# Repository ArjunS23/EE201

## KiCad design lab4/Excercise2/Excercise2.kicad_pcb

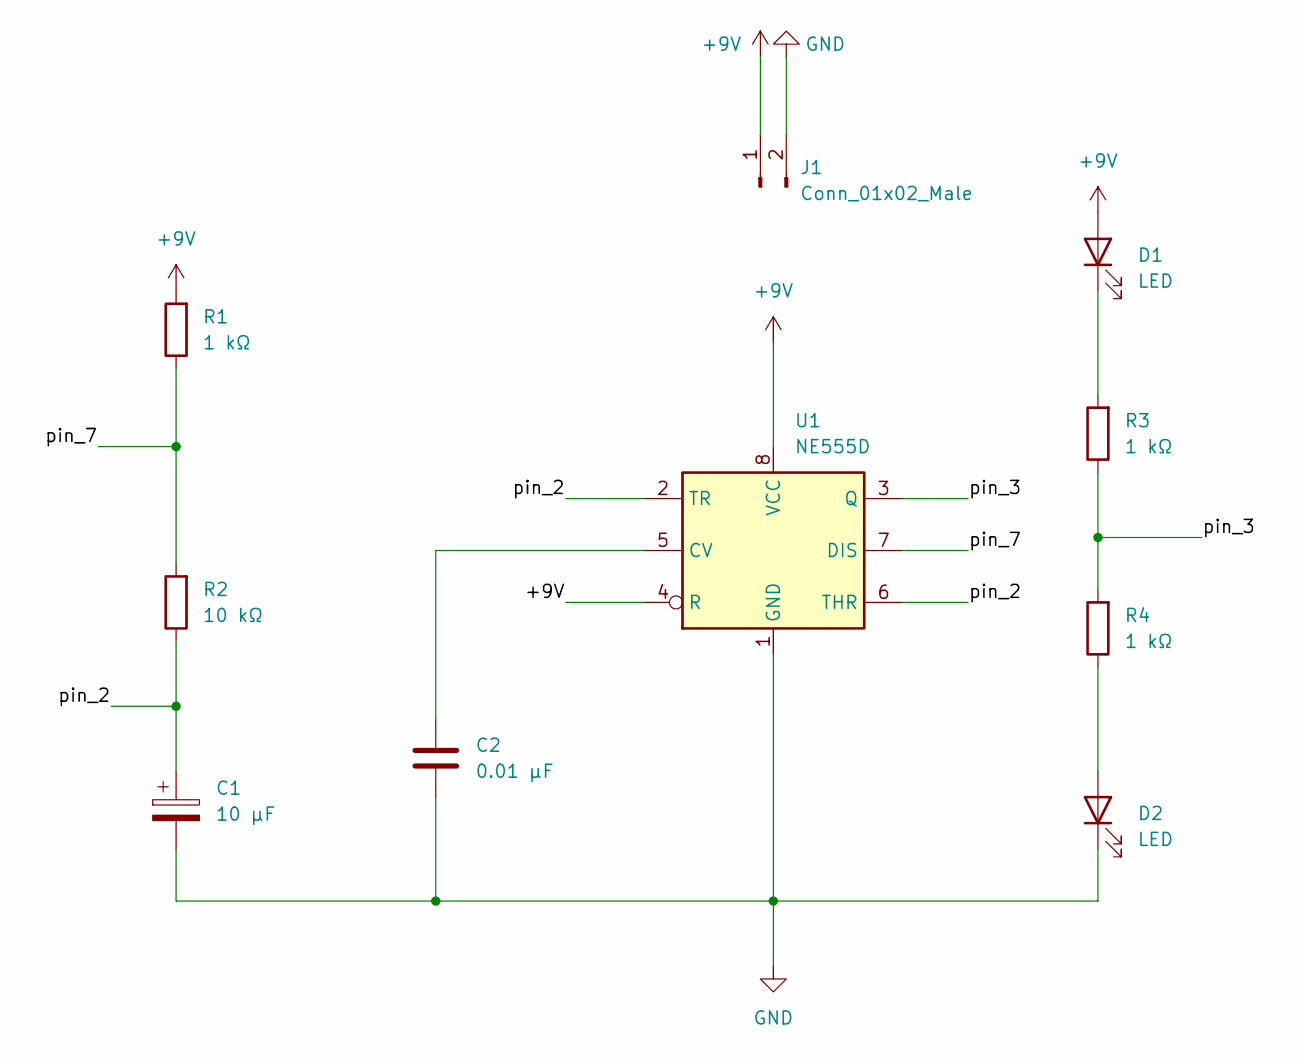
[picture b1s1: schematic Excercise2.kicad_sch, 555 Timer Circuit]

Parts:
C1: 10 μF; CP_EIA-3216-18_Kemet-A_Pad1.58x1.35mm_HandSolder
C2: 0.01 μF; C_0805_2012Metric_Pad1.18x1.45mm_HandSolder
D1, D2: LED; LED_1206_3216Metric_Pad1.42x1.75mm_HandSolder
J1: Conn_01x02_Male; TerminalBlock_bornier-2_P5.08mm
R1, R3, R4: 1 kΩ; R_0805_2012Metric_Pad1.20x1.40mm_HandSolder
R2: 10 kΩ; R_0805_2012Metric_Pad1.20x1.40mm_HandSolder
U1: NE555D; SOIC-8-1EP_3.9x4.9mm_P1.27mm_EP2.29x3mm

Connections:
+9V: D1.2 (A), J1.1, R1.2, U1.4 (R), U1.8 (VCC)
/pin_2: C1.1, R2.1, U1.2 (TR), U1.6 (THR)
/pin_3: R3.1, R4.2, U1.3 (Q)
/pin_7: R1.1, R2.2, U1.7 (DIS)
GND: C1.2, C2.2, D2.1 (K), J1.2, U1.1 (GND)
unnamed: C2.1, U1.5 (CV)
unnamed: D1.1 (K), R3.2
unnamed: D2.2 (A), R4.1

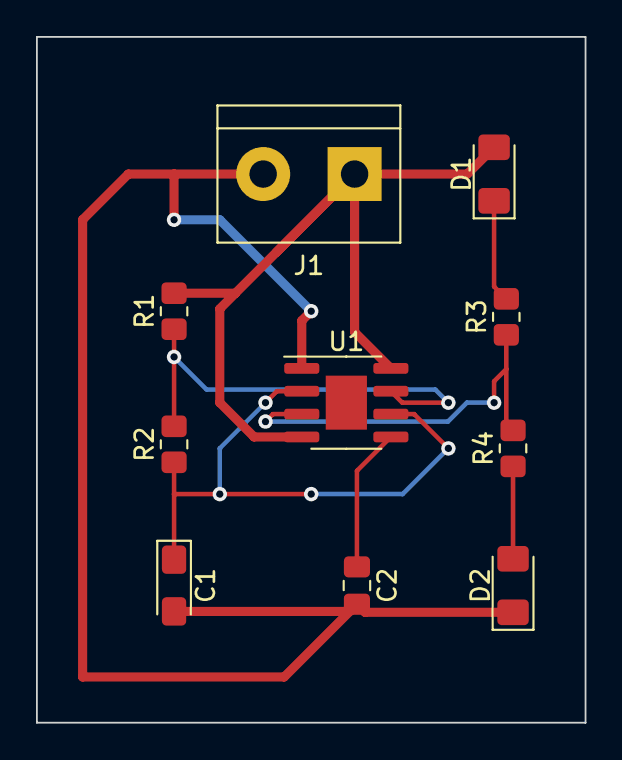
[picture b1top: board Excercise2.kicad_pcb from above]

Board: 2 copper layers, 30.5 x 38.1 mm, 10 parts (0 on the bottom side), 8 nets.

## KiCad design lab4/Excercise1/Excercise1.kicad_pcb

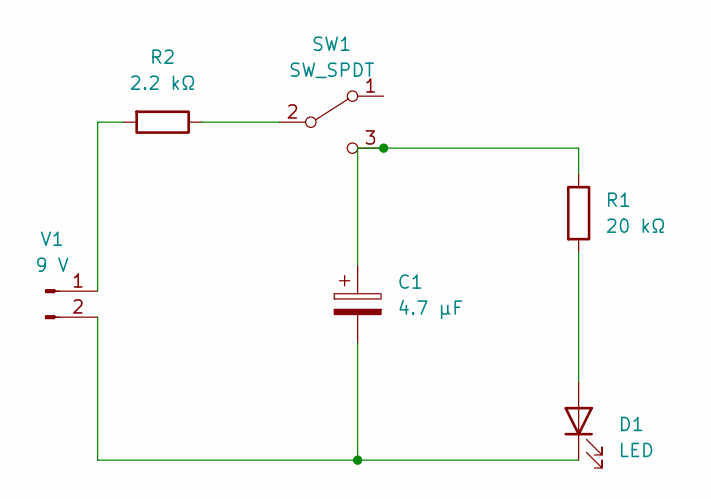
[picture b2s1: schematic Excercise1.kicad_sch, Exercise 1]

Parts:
C1: 4.7 μF; C_Radial_D5.0mm_H5.0mm_P2.00mm
D1: LED; LED_D5.0mm
R1: 20 kΩ; R_Axial_DIN0516_L15.5mm_D5.0mm_P20.32mm_Horizontal
R2: 2.2 kΩ; R_Axial_DIN0516_L15.5mm_D5.0mm_P20.32mm_Horizontal
SW1: SW_SPDT; SW_E-Switch_EG1224_SPDT_Angled
V1: 9 V; JST_PH_B2B-PH-K_1x02_P2.00mm_Vertical

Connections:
unnamed: C1.1, R1.1, SW1.3 (C)
unnamed: C1.2, D1.1 (K), V1.2
unnamed: D1.2 (A), R1.2
unnamed: R2.1, SW1.2 (B)
unnamed: R2.2, V1.1

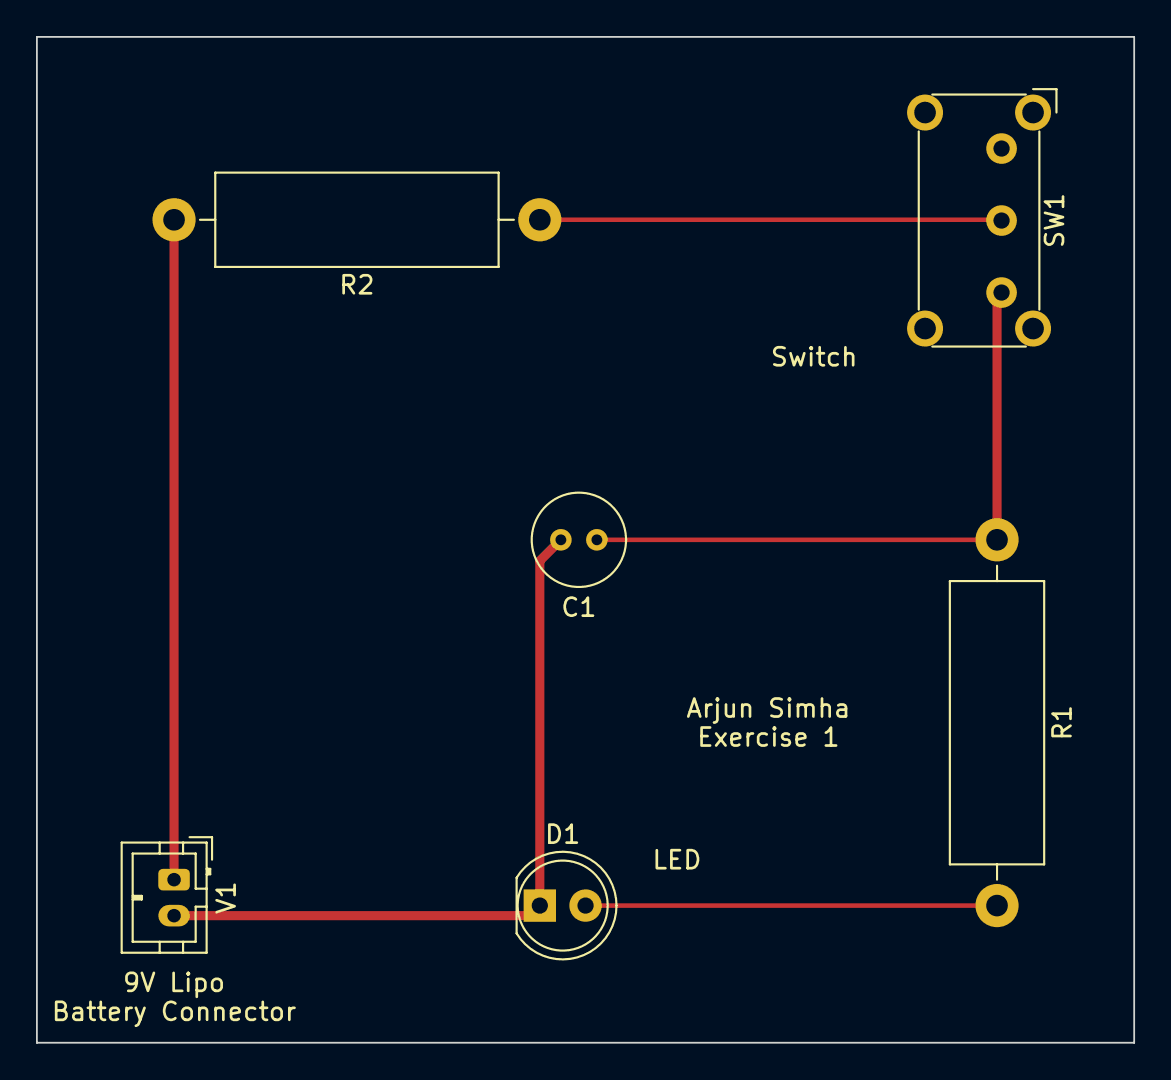
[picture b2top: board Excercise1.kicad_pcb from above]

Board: 2 copper layers, 61.0 x 55.9 mm, 6 parts (0 on the bottom side), 5 nets.

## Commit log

2023-01-13 Added Name
2023-01-13 Added Text
2023-01-13 Final Commit
2023-01-27 Updated projects
2023-02-03 Commit images
2023-02-10 Update Exercise 1
2023-02-11 Update Exercise 2
2023-02-17 Generated Gerber files
2023-03-10 added images
